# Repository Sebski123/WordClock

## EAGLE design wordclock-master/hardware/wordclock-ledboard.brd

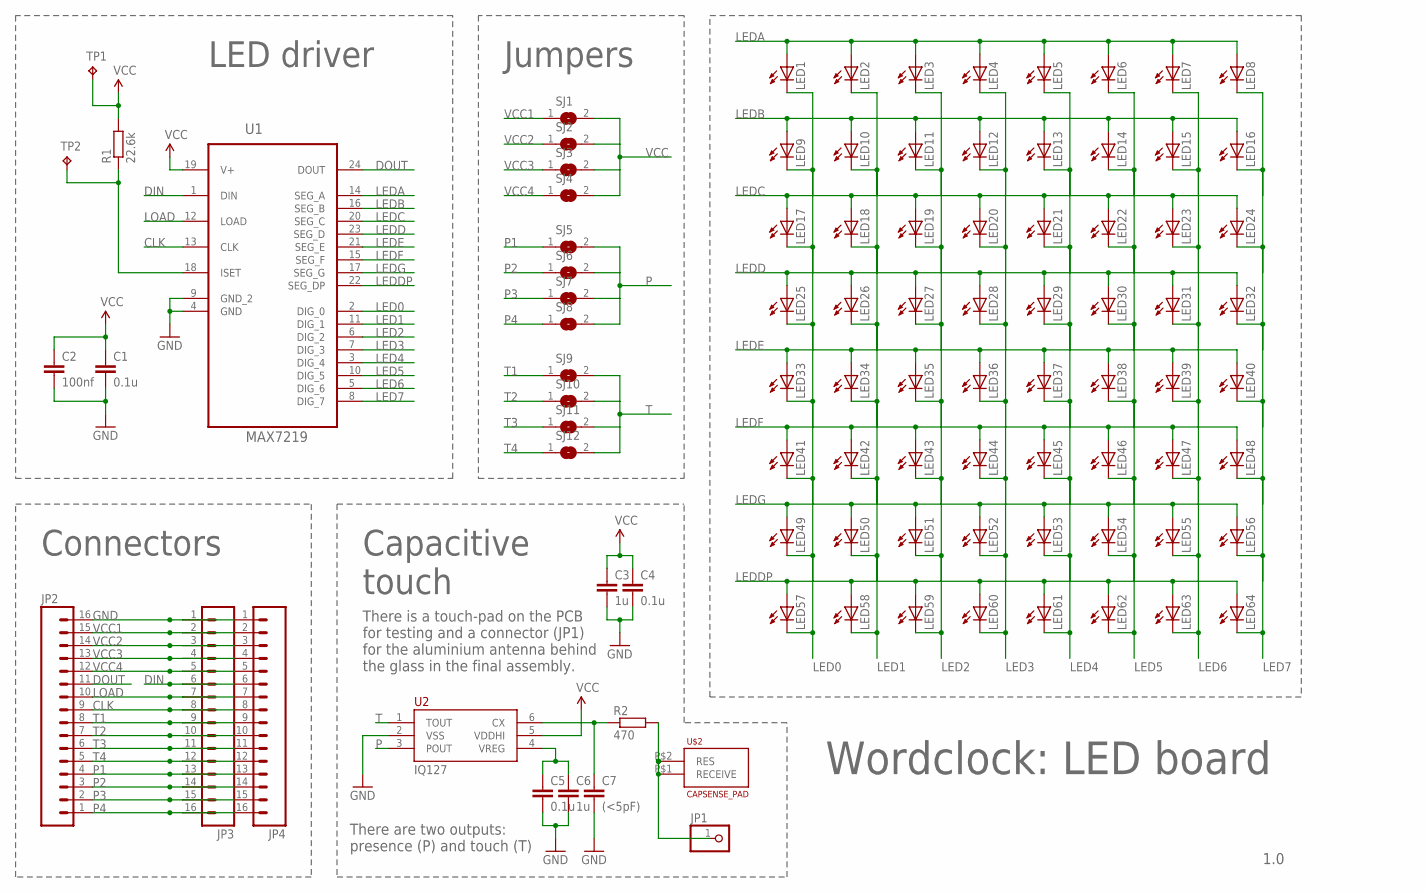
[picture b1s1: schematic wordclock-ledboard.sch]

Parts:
C1, C4, C5: 0.1u; C0805
C2: 100nf; C0805
C3, C6: 1u; C0805
C7: (<5pF); C0805
JP1: PINHD-1X1; 1X01
JP2, JP3, JP4: M161X16_NO_SILK; 1X16_NO_SILK
LED1, LED2, LED3, LED4, LED5, LED6, LED7, LED8, LED9, LED10, LED11, LED12, LED13, LED14, LED15, LED16, LED17, LED18, LED19, LED20, LED21, LED22, LED23, LED24, LED25, LED26, LED27, LED28, LED29, LED30, LED31, LED32, LED33, LED34, LED35, LED36, LED37, LED38, LED39, LED40, LED41, LED42, LED43, LED44, LED45, LED46, LED47, LED48, LED49, LED50, LED51, LED52, LED53, LED54, LED55, LED56, LED57, LED58, LED59, LED60, LED61, LED62, LED63, LED64: LEDKA-3528ASYC; KA-3528ASYC
R1: 22.6k; R0603
R2: 470; R0603
SJ1, SJ2, SJ3, SJ4, SJ5, SJ6, SJ7, SJ8, SJ9, SJ10, SJ11, SJ12: SJW
TP1, TP2: TPTP20R; TP20R
U1: MAX7219; SOIC127P1032X265-24N
U2: IQ127; TSOT-23-6
U$2: CAPSENSE_PAD

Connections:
C6: C5.1, C6.1, U2.4 (VREG)
CLK: JP2.9, JP3.8, JP4.8, U1.13 (CLK)
DIN: JP3.6, JP4.6, U1.1 (DIN)
DOUT: JP2.11, U1.24 (DOUT)
GND: C1.2, C2.2, C3.2, C4.2, C5.2, C6.2, C7.2, JP2.16, JP3.1, JP4.1, U1.4 (GND), U1.9 (GND_2), U2.2 (VSS)
LED0: LED1.C, LED9.C, LED17.C, LED25.C, LED33.C, LED41.C, LED49.C, LED57.C, U1.2 (DIG_0)
LED1: LED2.C, LED10.C, LED18.C, LED26.C, LED34.C, LED42.C, LED50.C, LED58.C, U1.11 (DIG_1)
LED2: LED3.C, LED11.C, LED19.C, LED27.C, LED35.C, LED43.C, LED51.C, LED59.C, U1.6 (DIG_2)
LED3: LED4.C, LED12.C, LED20.C, LED28.C, LED36.C, LED44.C, LED52.C, LED60.C, U1.7 (DIG_3)
LED4: LED5.C, LED13.C, LED21.C, LED29.C, LED37.C, LED45.C, LED53.C, LED61.C, U1.3 (DIG_4)
LED5: LED6.C, LED14.C, LED22.C, LED30.C, LED38.C, LED46.C, LED54.C, LED62.C, U1.10 (DIG_5)
LED6: LED7.C, LED15.C, LED23.C, LED31.C, LED39.C, LED47.C, LED55.C, LED63.C, U1.5 (DIG_6)
LED7: LED8.C, LED16.C, LED24.C, LED32.C, LED40.C, LED48.C, LED56.C, LED64.C, U1.8 (DIG_7)
LEDA: LED1.A, LED2.A, LED3.A, LED4.A, LED5.A, LED6.A, LED7.A, LED8.A, U1.14 (SEG_A)
LEDB: LED9.A, LED10.A, LED11.A, LED12.A, LED13.A, LED14.A, LED15.A, LED16.A, U1.16 (SEG_B)
LEDC: LED17.A, LED18.A, LED19.A, LED20.A, LED21.A, LED22.A, LED23.A, LED24.A, U1.20 (SEG_C)
LEDD: LED25.A, LED26.A, LED27.A, LED28.A, LED29.A, LED30.A, LED31.A, LED32.A, U1.23 (SEG_D)
LEDDP: LED57.A, LED58.A, LED59.A, LED60.A, LED61.A, LED62.A, LED63.A, LED64.A, U1.22 (SEG_DP)
LEDE: LED33.A, LED34.A, LED35.A, LED36.A, LED37.A, LED38.A, LED39.A, LED40.A, U1.21 (SEG_E)
LEDF: LED41.A, LED42.A, LED43.A, LED44.A, LED45.A, LED46.A, LED47.A, LED48.A, U1.15 (SEG_F)
LEDG: LED49.A, LED50.A, LED51.A, LED52.A, LED53.A, LED54.A, LED55.A, LED56.A, U1.17 (SEG_G)
LOAD: JP2.10, JP3.7, JP4.7, U1.12 (LOAD)
unnamed: JP1.1, R2.2, U$2.P$1 (RECEIVE), U$2.P$2 (RES)
unnamed: R1.1, TP2.TP, U1.18 (ISET)
unnamed: C7.1, R2.1, U2.6 (CX)
P: SJ5.2, SJ6.2, SJ7.2, SJ8.2, U2.3 (POUT)
P1: JP2.4, JP3.13, JP4.13, SJ5.1
P2: JP2.3, JP3.14, JP4.14, SJ6.1
P3: JP2.2, JP3.15, JP4.15, SJ7.1
P4: JP2.1, JP3.16, JP4.16, SJ8.1
T: SJ9.2, SJ10.2, SJ11.2, SJ12.2, U2.1 (TOUT)
T1: JP2.8, JP3.9, JP4.9, SJ9.1
T2: JP2.7, JP3.10, JP4.10, SJ10.1
T3: JP2.6, JP3.11, JP4.11, SJ11.1
T4: JP2.5, JP3.12, JP4.12, SJ12.1
VCC: C1.1, C2.1, C3.1, C4.1, R1.2, SJ1.2, SJ2.2, SJ3.2, SJ4.2, TP1.TP, U1.19 (V+), U2.5 (VDDHI)
VCC1: JP2.15, JP3.2, JP4.2, SJ1.1
VCC2: JP2.14, JP3.3, JP4.3, SJ2.1
VCC3: JP2.13, JP3.4, JP4.4, SJ3.1
VCC4: JP2.12, JP3.5, JP4.5, SJ4.1

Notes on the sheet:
Wordclock: LED board
1.0
LED driver
Jumpers
IQ127
Capacitive touch
Connectors
There is a touch-pad on the PCB for testing and a connector (JP1) for the aluminium antenna behind the glass in the final assembly.
There are two outputs: presence (P) and touch (T)

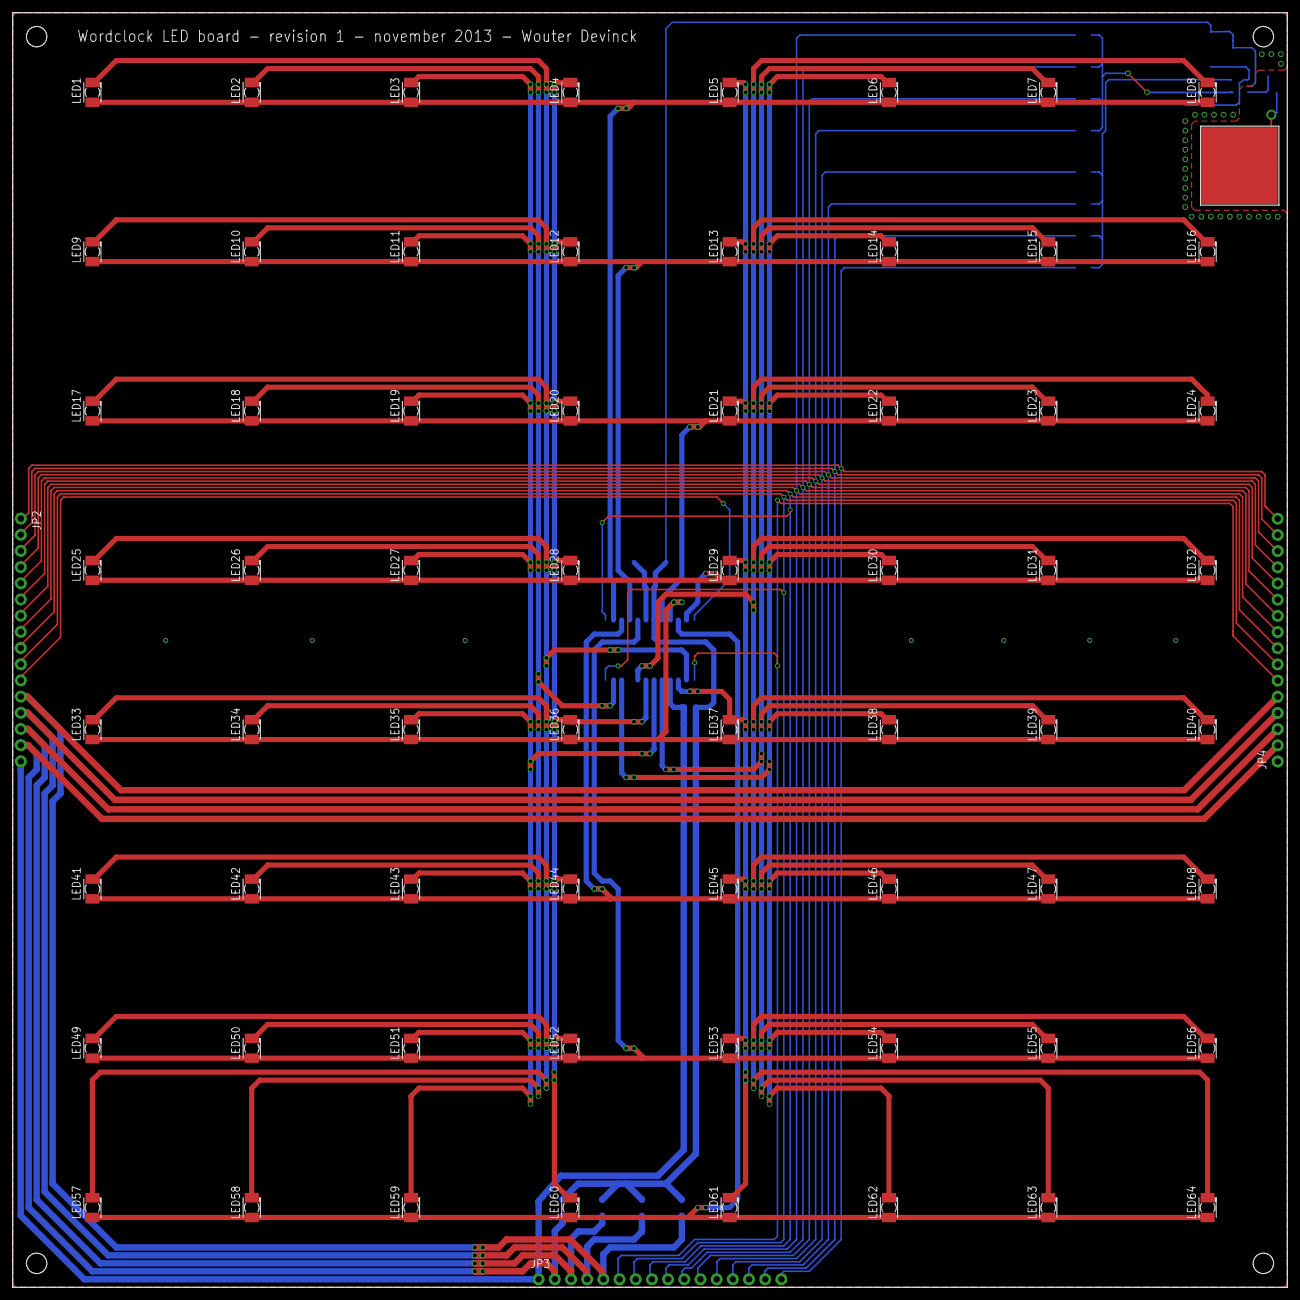
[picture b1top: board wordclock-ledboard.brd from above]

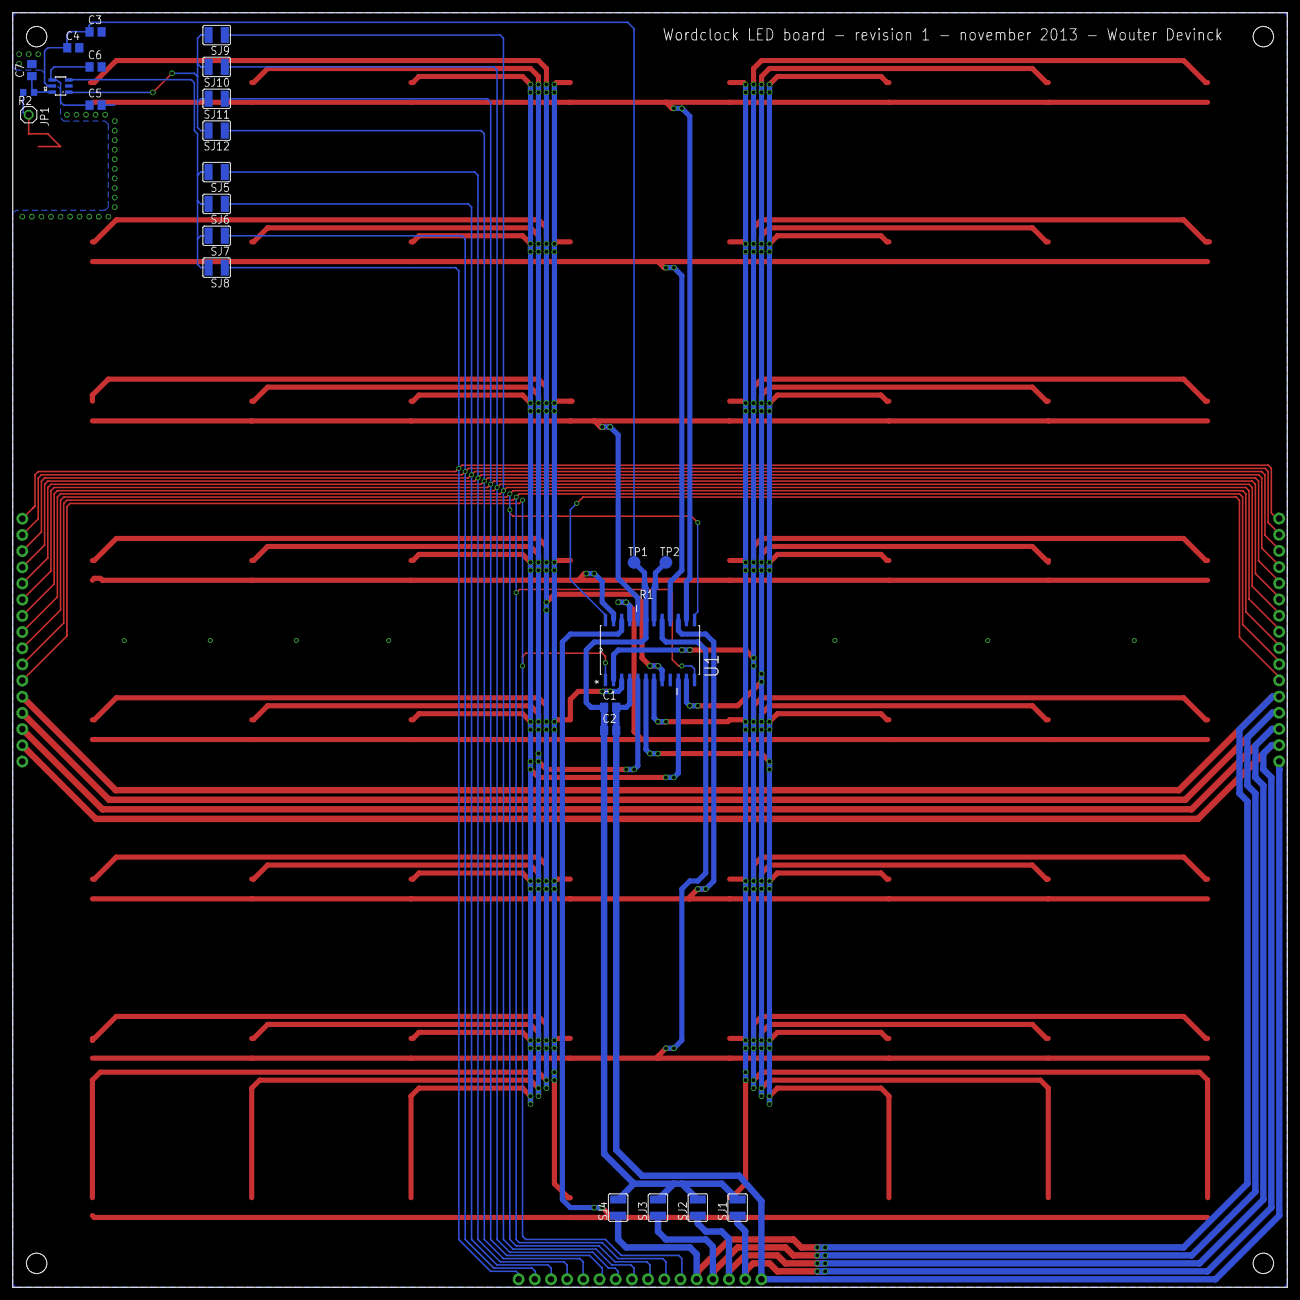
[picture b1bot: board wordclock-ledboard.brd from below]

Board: 4 copper layers, 200.0 x 200.0 mm, 94 parts (26 on the bottom side), 40 nets.

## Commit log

2021-12-01 Add trippy shit
2021-12-01 fix pins
2021-12-01 update gitignore
2021-12-03 Update to work on sebskis clock
2021-12-03 delet
2021-12-04 Added scrolling text animation

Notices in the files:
parts and their libraries:
SparkFun-Connectors: Licensing: CC v3.0 Share-Alike You are welcome to use this library for commercial purposes.
